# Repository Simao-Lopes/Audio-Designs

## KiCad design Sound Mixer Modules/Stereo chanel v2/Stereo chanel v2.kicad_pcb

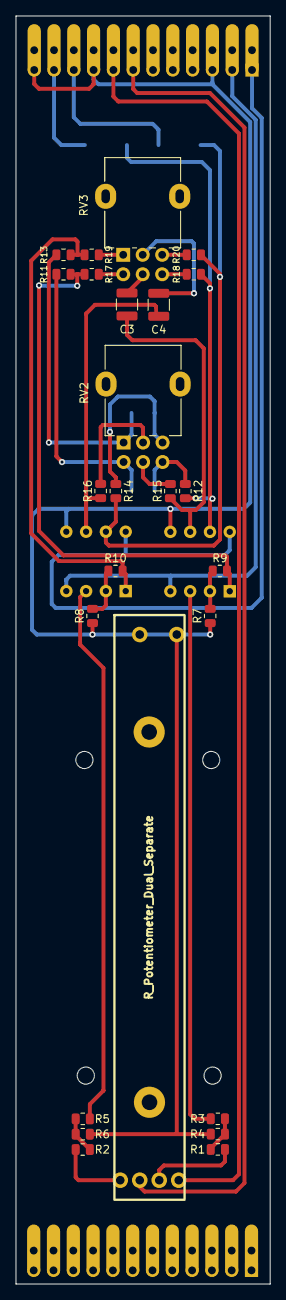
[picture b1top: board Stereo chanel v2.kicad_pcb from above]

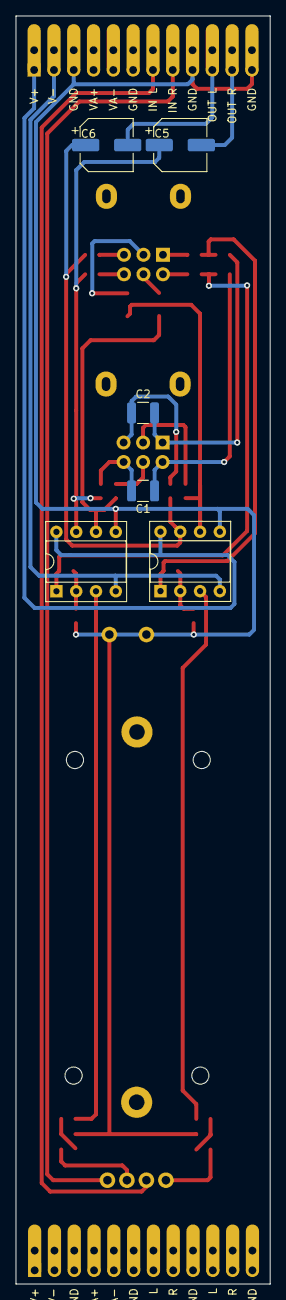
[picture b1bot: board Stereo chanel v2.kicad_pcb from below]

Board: 2 copper layers, 32.6 x 162.7 mm, 33 parts (8 on the bottom side), 33 nets.

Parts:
C1, C2: 47N; C_1210_3225Metric
C3, C4: 1N; C_1210_3225Metric
C5, C6: 10uf; CP_Elec_6.3x5.4_Nichicon
J1: Conector IO; PinHeader_2x12_P2.54mm_Vertical
J2: DUMMY; PinHeader_2x12_P2.54mm_Vertical
R1, R2, R3, R5: 2K2; R_0805_2012Metric
R4, R6: 100K; R_0805_2012Metric
R7, R8, R9, R10, R17, R18, R19, R20: 10K; R_0805_2012Metric
R11, R12, R13, R14, R15, R16: 22K; R_0805_2012Metric
RV1: R_Potentiometer_Dual_Separate; ALPS RS60112
RV2, RV3: R_Potentiometer_Dual_Separate; Potentiometer_Alpha_RD902F-40-00D_Dual_Vertical
U1, U2: NE5532; DIP-8_W7.62mm_Socket

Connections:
GND: J1.3, J1.9, J1.12, R4.1, R6.1, R7.1, R8.1, RV1.3, RV1.6, U1.5 (+), U2.5 (+)
L_INPUT: J1.7, RV1.1
L_OUTPUT: C6.2, J1.10
unnamed: C1.1, R11.1, RV2.4
unnamed: C1.2, R12.2, RV2.6
unnamed: C2.1, R13.1, RV2.1
unnamed: C2.2, R14.2, RV2.3
unnamed: C3.1, R15.1, U1.6 (-)
unnamed: C3.2, RV3.5
unnamed: C4.1, R16.1, U2.6 (-)
unnamed: C4.2, RV3.2
unnamed: C5.1, R12.1, R18.1, U1.7
unnamed: C6.1, R14.1, R20.1, U2.7
unnamed: R1.1, RV1.5
unnamed: R1.2, R3.1, R4.2
unnamed: R2.1, RV1.2
unnamed: R2.2, R5.1, R6.2
unnamed: R3.2, U1.3 (+)
unnamed: R5.2, U2.3 (+)
unnamed: R7.2, R9.2, U1.2 (-)
unnamed: R10.1, R13.2, R19.2, U2.1
unnamed: R8.2, R10.2, U2.2 (-)
unnamed: R9.1, R11.2, R17.2, U1.1
unnamed: R15.2, RV2.5
unnamed: R16.2, RV2.2
unnamed: R17.1, RV3.4
unnamed: R18.2, RV3.6
unnamed: R19.1, RV3.1
unnamed: R20.2, RV3.3
R_INPUT: J1.8, RV1.4
R_OUTPUT: C5.2, J1.11
VCC: J1.1, U1.8 (V+), U2.8 (V+)
VEE: J1.2, U1.4 (V-), U2.4 (V-)

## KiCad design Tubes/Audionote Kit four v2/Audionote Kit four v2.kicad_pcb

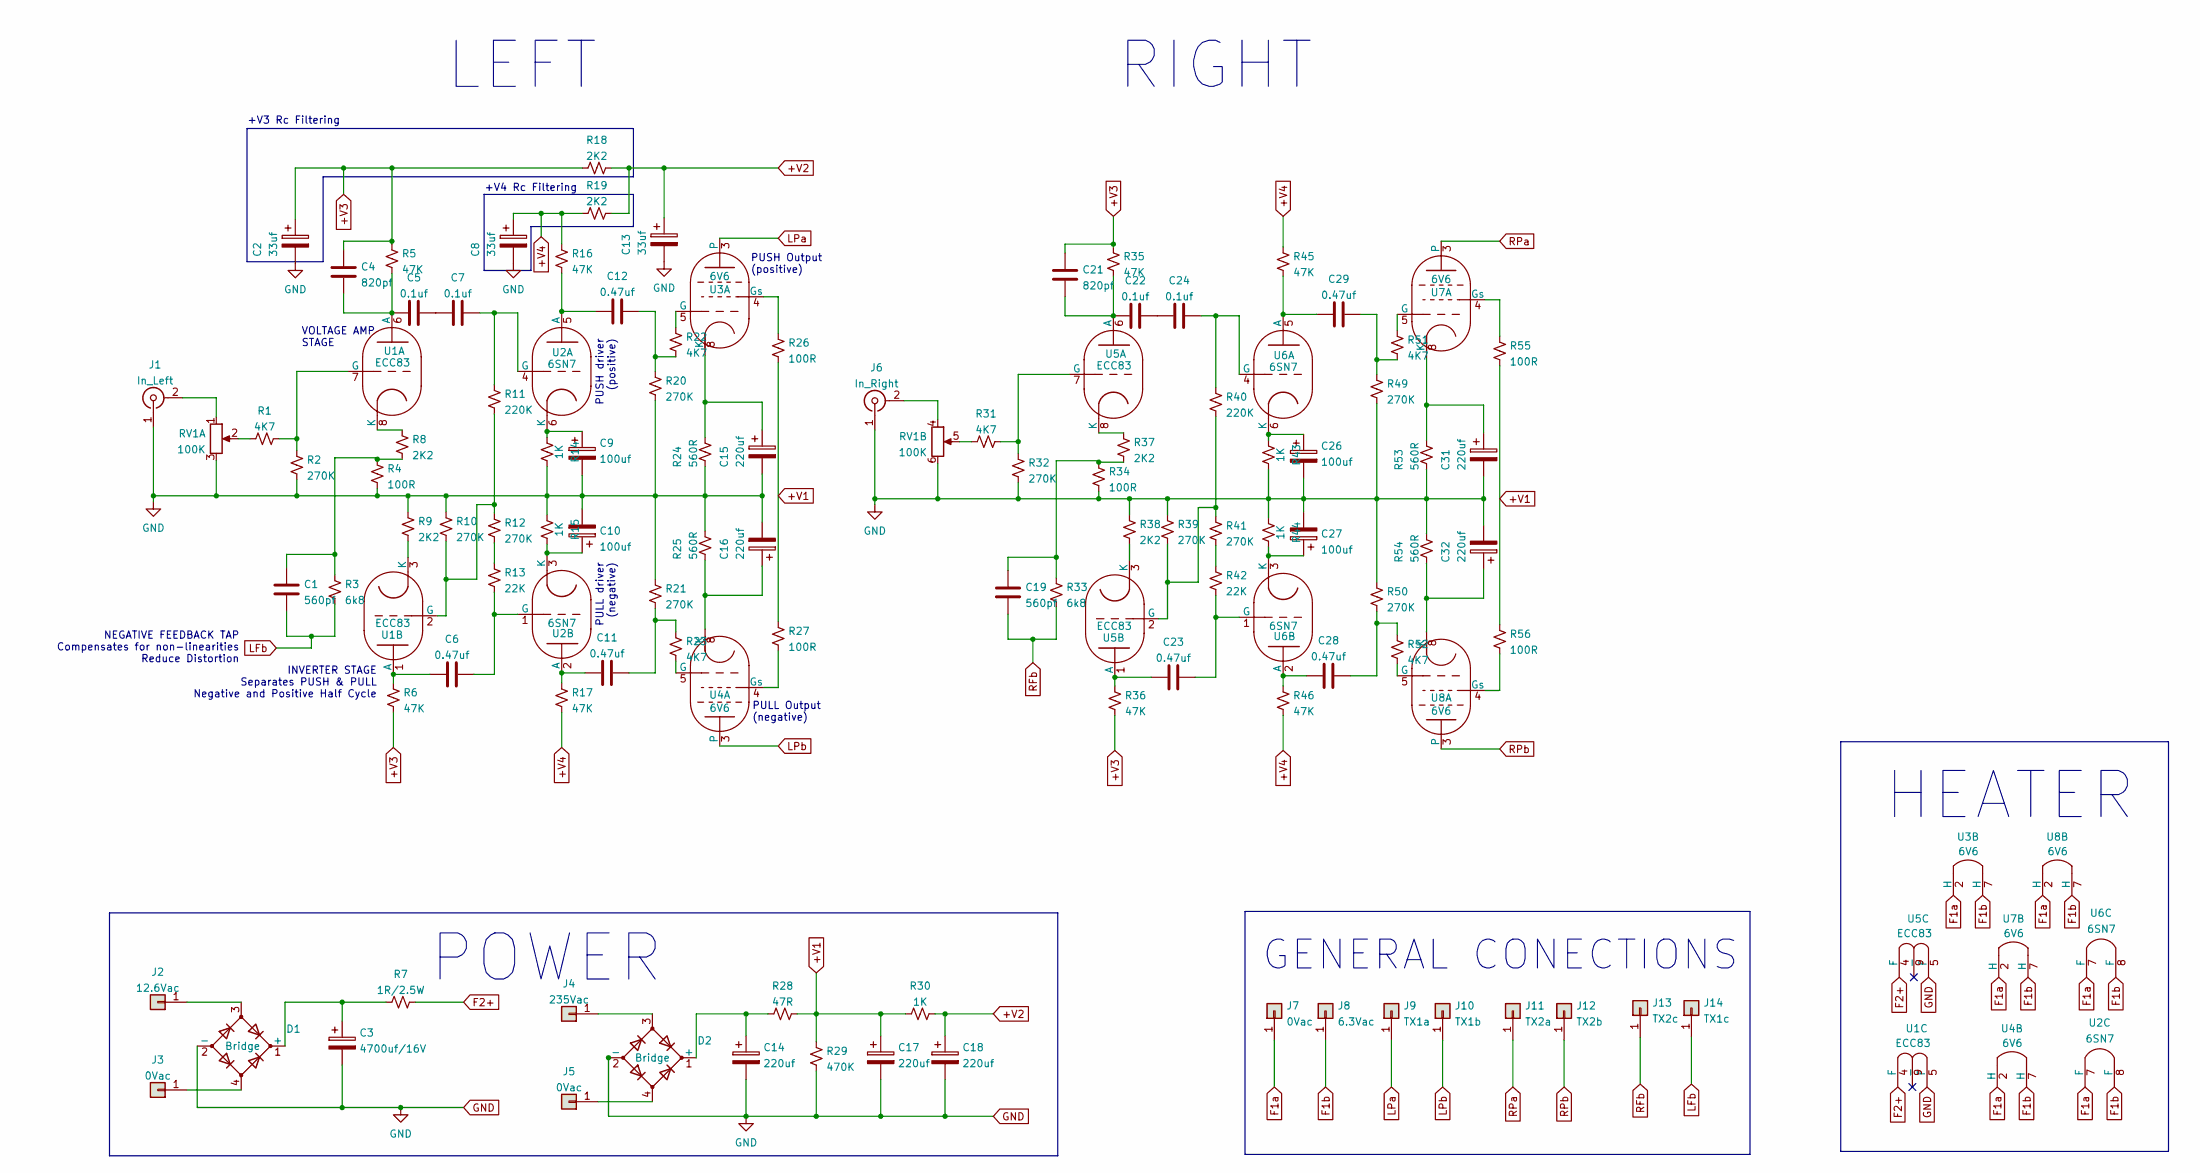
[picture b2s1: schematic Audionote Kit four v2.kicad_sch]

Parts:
C1, C19: 560pf; C_Rect_L7.2mm_W3.5mm_P5.00mm_FKS2_FKP2_MKS2_MKP2
C2, C8, C13: 33uf; CP_Radial_D10.0mm_P5.00mm_P7.50mm
C3: 4700uf/16V; C_Radial_D16.0mm_H31.5mm_P7.50mm
C4, C21: 820pf; C_Rect_L7.2mm_W3.5mm_P5.00mm_FKS2_FKP2_MKS2_MKP2
C5, C7, C22, C24: 0.1uf; C_Rect_L26.5mm_W6.0mm_P22.50mm_MKS4
C6, C11, C12, C23, C28, C29: 0.47uf; C_Rect_L31.5mm_W9.0mm_P27.50mm_MKS4
C9, C10, C26, C27: 100uf; CP_Radial_D6.3mm_P2.50mm
C14, C17, C18: 220uf; CP_Radial_D25.0mm_P10.00mm_SnapIn
C15, C16, C31, C32: 220uf; CP_Radial_D10.0mm_P5.00mm_P7.50mm
D1, D2: Bridge; Diode_Bridge_19.0x3.5x10.0mm_P5.0mm
J1: In_Left; SolderWire-0.75sqmm_1x02_P7mm_D1.25mm_OD3.5mm
J2: 12.6Vac; SolderWire-0.75sqmm_1x01_D1.25mm_OD2.3mm
J3, J5, J7: 0Vac; SolderWire-0.75sqmm_1x01_D1.25mm_OD2.3mm
J4: 235Vac; SolderWire-0.75sqmm_1x01_D1.25mm_OD2.3mm
J6: In_Right; SolderWire-0.75sqmm_1x02_P7mm_D1.25mm_OD3.5mm
J8: 6.3Vac; SolderWire-0.75sqmm_1x01_D1.25mm_OD2.3mm
J9: TX1a; SolderWire-0.75sqmm_1x01_D1.25mm_OD2.3mm
J10: TX1b; SolderWire-0.75sqmm_1x01_D1.25mm_OD2.3mm
J11: TX2a; SolderWire-0.75sqmm_1x01_D1.25mm_OD2.3mm
J12: TX2b; SolderWire-0.75sqmm_1x01_D1.25mm_OD2.3mm
J13: TX2c; SolderWire-0.75sqmm_1x01_D1.25mm_OD2.3mm
J14: TX1c; SolderWire-0.75sqmm_1x01_D1.25mm_OD2.3mm
R1, R22, R23, R31, R51, R52: 4K7; R_Axial_DIN0309_L9.0mm_D3.2mm_P12.70mm_Horizontal
R2, R10, R12, R20, R21, R32, R39, R41, R49, R50: 270K; R_Axial_DIN0309_L9.0mm_D3.2mm_P12.70mm_Horizontal
R3, R33: 6k8; R_Axial_DIN0309_L9.0mm_D3.2mm_P12.70mm_Horizontal
R4, R34: 100R; R_Axial_DIN0309_L9.0mm_D3.2mm_P12.70mm_Horizontal
R5, R6, R16, R17, R35, R36, R45, R46: 47K; R_Axial_DIN0309_L9.0mm_D3.2mm_P12.70mm_Horizontal
R7: 1R/2.5W; R_Axial_DIN0414_L11.9mm_D4.5mm_P15.24mm_Horizontal
R8, R9, R18, R19, R37, R38: 2K2; R_Axial_DIN0414_L11.9mm_D4.5mm_P15.24mm_Horizontal
R11, R40: 220K; R_Axial_DIN0309_L9.0mm_D3.2mm_P12.70mm_Horizontal
R13, R42: 22K; R_Axial_DIN0309_L9.0mm_D3.2mm_P12.70mm_Horizontal
R14, R15, R43, R44: 1K; R_Axial_DIN0309_L9.0mm_D3.2mm_P12.70mm_Horizontal
R24, R25, R53, R54: 560R; R_Axial_DIN0414_L11.9mm_D4.5mm_P15.24mm_Horizontal
R26, R27, R55, R56: 100R; R_Axial_DIN0414_L11.9mm_D4.5mm_P15.24mm_Horizontal
R28: 47R; R_Axial_Power_L25.0mm_W9.0mm_P27.94mm
R29: 470K; R_Axial_Power_L25.0mm_W9.0mm_P27.94mm
R30: 1K; R_Axial_Power_L25.0mm_W9.0mm_P27.94mm
RV1: 100K; Potentiometer_Alps_RK097_Dual_Horizontal
U1, U5: ECC83; Valve_Noval_P
U2, U6: 6SN7; Valve_Octal
U3, U4, U7, U8: 6V6; Valve_Octal

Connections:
+V1: C17.1, R26.2, R27.1, R28.2, R29.2, R30.1, R55.2, R56.1
+V2: C13.1, C18.1, R18.1, R19.1, R30.2
+V3: C2.1, C4.1, C21.1, R5.2, R6.1, R18.2, R35.2, R36.1; also elsewhere on the board
+V4: C8.1, R16.2, R17.1, R19.2, R45.2, R46.1
F1a: J7.1, U2.7 (F), U3.2 (H), U4.2 (H), U6.7 (F), U7.2 (H), U8.2 (H); also elsewhere on the board
F1b: J8.1, U2.8 (F), U3.7 (H), U4.7 (H), U6.8 (F), U7.7 (H), U8.7 (H); also elsewhere on the board
F2+: R7.2, U1.4 (F), U5.4 (F)
GND: C2.2, C3.2, C8.2, C9.2, C10.2, C13.2, C14.2, C15.2, C16.2, C17.2, C18.2, C26.2, C27.2, C31.2, C32.2, D1.2 (-), D2.2 (-), J1.1 (In), J6.1 (In), R2.1, R4.1, R9.2, R10.2, R14.2, R15.1, R20.1, R21.2, R24.1, R25.1, R29.1, R32.1, R34.1, R38.2, R39.2, R43.2, R44.1, R49.1, R50.2, R53.1, R54.1, RV1.3, RV1.6, U1.5 (F), U5.5 (F); also elsewhere on the board
LFb: C1.1, J14.1, R3.2; also elsewhere on the board
LPa: J9.1, U3.3
LPb: J10.1, U4.3
unnamed 11: C1.2, R3.1, R4.2, R8.1; also elsewhere on the board
unnamed: C3.1, D1.1 (+), R7.1
unnamed 13: C4.2, C5.1, R5.1, U1.6 (A); also elsewhere on the board
unnamed: C5.2, C7.1
unnamed: C6.1, R6.2, U1.1 (A)
unnamed: C6.2, R13.1, U2.1 (G)
unnamed: C7.2, R11.2, U2.4 (G)
unnamed: C9.1, R14.1, U2.6 (K)
unnamed: C10.1, R15.2, U2.3 (K)
unnamed: C11.1, R17.2, U2.2 (A)
unnamed: C11.2, R21.1, R23.2
unnamed: C12.1, R16.1, U2.5 (A)
unnamed: C12.2, R20.2, R22.1
unnamed: C14.1, D2.1 (+), R28.1
unnamed: C15.1, R24.2, U3.8 (K)
unnamed: C16.1, R25.2, U4.8 (K)
unnamed: C19.2, R33.1, R34.2, R37.1
unnamed 28: C21.2, C22.1, R35.1, U5.6 (A); also elsewhere on the board
unnamed: C22.2, C24.1
unnamed: C23.1, R36.2, U5.1 (A)
unnamed: C23.2, R42.1, U6.1 (G)
unnamed: C24.2, R40.2, U6.4 (G)
unnamed: C26.1, R43.1, U6.6 (K)
unnamed: C27.1, R44.2, U6.3 (K)
unnamed: C28.1, R46.2, U6.2 (A)
unnamed: C28.2, R50.1, R52.2
unnamed: C29.1, R45.1, U6.5 (A)
unnamed: C29.2, R49.2, R51.1
unnamed: C31.1, R53.2, U7.8 (K)
unnamed: C32.1, R54.2, U8.8 (K)
unnamed: D1.3, J2.1
unnamed: D1.4, J3.1
unnamed: D2.3, J4.1
unnamed: D2.4, J5.1
unnamed: J1.2 (Ext), RV1.1
unnamed: J6.2 (Ext), RV1.4
unnamed 47: R1.1, RV1.2; also elsewhere on the board
unnamed: R1.2, R2.2, U1.7 (G)
unnamed: R8.2, U1.8 (K)
unnamed: R9.1, U1.3 (K)
unnamed: R10.1, R11.1, R12.2, U1.2 (G)
unnamed: R12.1, R13.2
unnamed: R22.2, U3.5 (G)
unnamed: R23.1, U4.5 (G)
unnamed: R26.1, U3.4 (Gs)
unnamed: R27.2, U4.4 (Gs)
unnamed 57: R31.1, RV1.5; also elsewhere on the board
unnamed: R31.2, R32.2, U5.7 (G)
unnamed: R37.2, U5.8 (K)
unnamed: R38.1, U5.3 (K)
unnamed: R39.1, R40.1, R41.2, U5.2 (G)
unnamed: R41.1, R42.2
unnamed: R51.2, U7.5 (G)
unnamed: R52.1, U8.5 (G)
unnamed: R55.1, U7.4 (Gs)
unnamed: R56.2, U8.4 (Gs)
RFb: C19.1, J13.1, R33.2; also elsewhere on the board
RPa: J11.1, U7.3
RPb: J12.1, U8.3

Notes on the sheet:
GENERAL CONECTIONS
+V4 Rc Filtering
INVERTER STAGE Separates PUSH & PULL Negative and Positive Half Cycle
RIGHT
VOLTAGE AMP STAGE
POWER
PUSH driver (positive)
PUSH Output (positive)
NEGATIVE FEEDBACK TAP Compensates for non-linearities Reduce Distortion
PULL driver (negative)
PULL Output (negative)
LEFT
+V3 Rc Filtering
HEATER

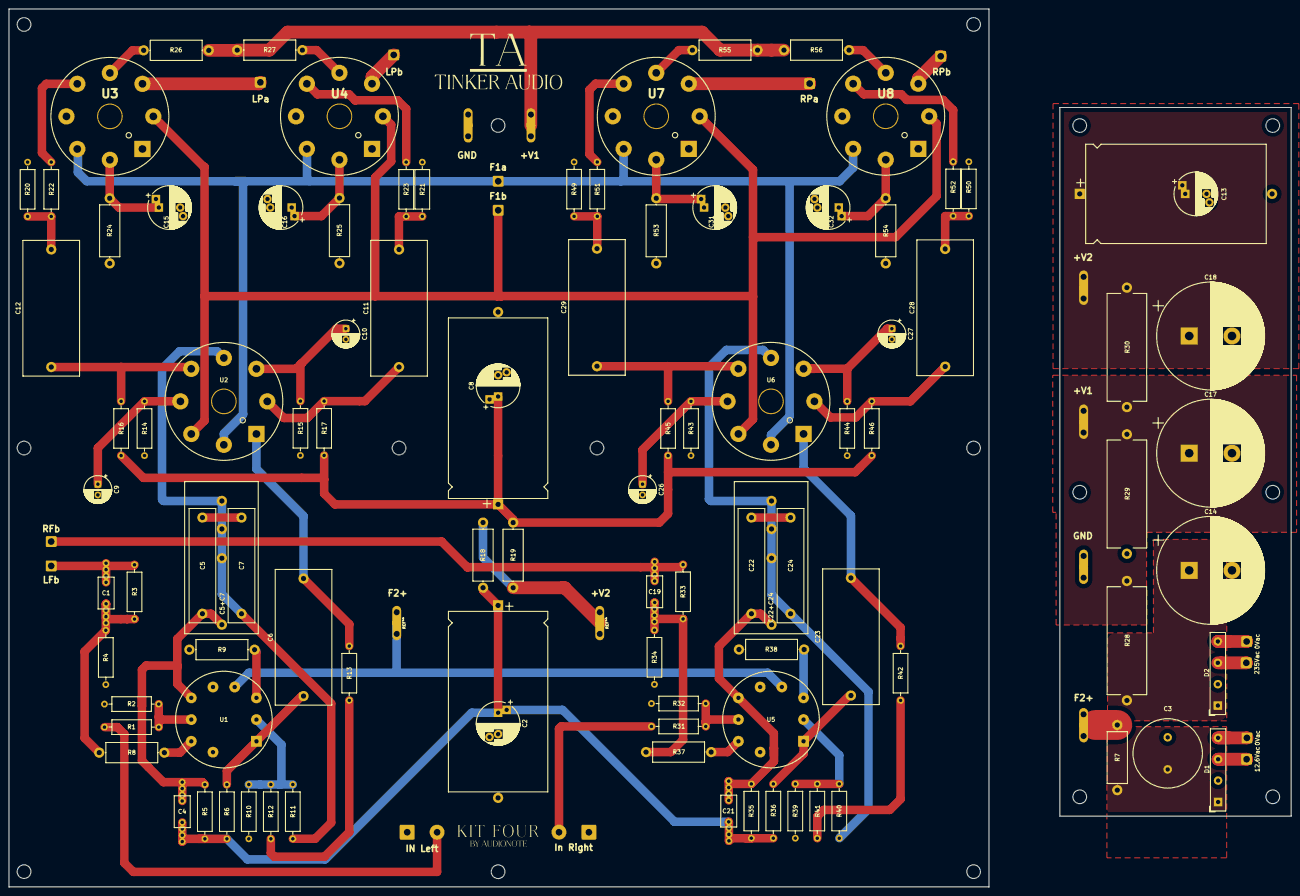
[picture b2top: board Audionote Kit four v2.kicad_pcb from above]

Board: 2 copper layers, 229.2 x 205.4 mm, 117 parts (0 on the bottom side), 68 nets.

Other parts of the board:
1, 2, 3, 4, 5, 6, 7, 8, 9, 10: (no value)
F1a: 6.3Vac; SolderWire-0.75sqmm_1x01_D1.25mm_OD2.3mm
F1b: 0Vac; SolderWire-0.75sqmm_1x01_D1.25mm_OD2.3mm
IN Left: In_Left; SolderWire-0.75sqmm_1x02_P7mm_D1.25mm_OD3.5mm
In Right : In_Right; SolderWire-0.75sqmm_1x02_P7mm_D1.25mm_OD3.5mm
LFb: TX1c; SolderWire-0.75sqmm_1x01_D1.25mm_OD2.3mm
RFb: TX2c; SolderWire-0.75sqmm_1x01_D1.25mm_OD2.3mm

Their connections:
+V3: 3.1, 4.1, 5.1, 6.1; also elsewhere on the board
F1a: F1b.1; also elsewhere on the board
F1b: F1a.1; also elsewhere on the board
GND: IN Left.1 (In), In Right.1 (In); also elsewhere on the board
LFb: LFb.1; also elsewhere on the board
unnamed 11: 9.2, 10.2; also elsewhere on the board
unnamed 13: 7.2, 8.2; also elsewhere on the board
unnamed 28: 1.2, 2.2; also elsewhere on the board
unnamed 47: IN Left.2 (Ext); also elsewhere on the board
unnamed 57: In Right.2 (Ext); also elsewhere on the board
RFb: RFb.1; also elsewhere on the board

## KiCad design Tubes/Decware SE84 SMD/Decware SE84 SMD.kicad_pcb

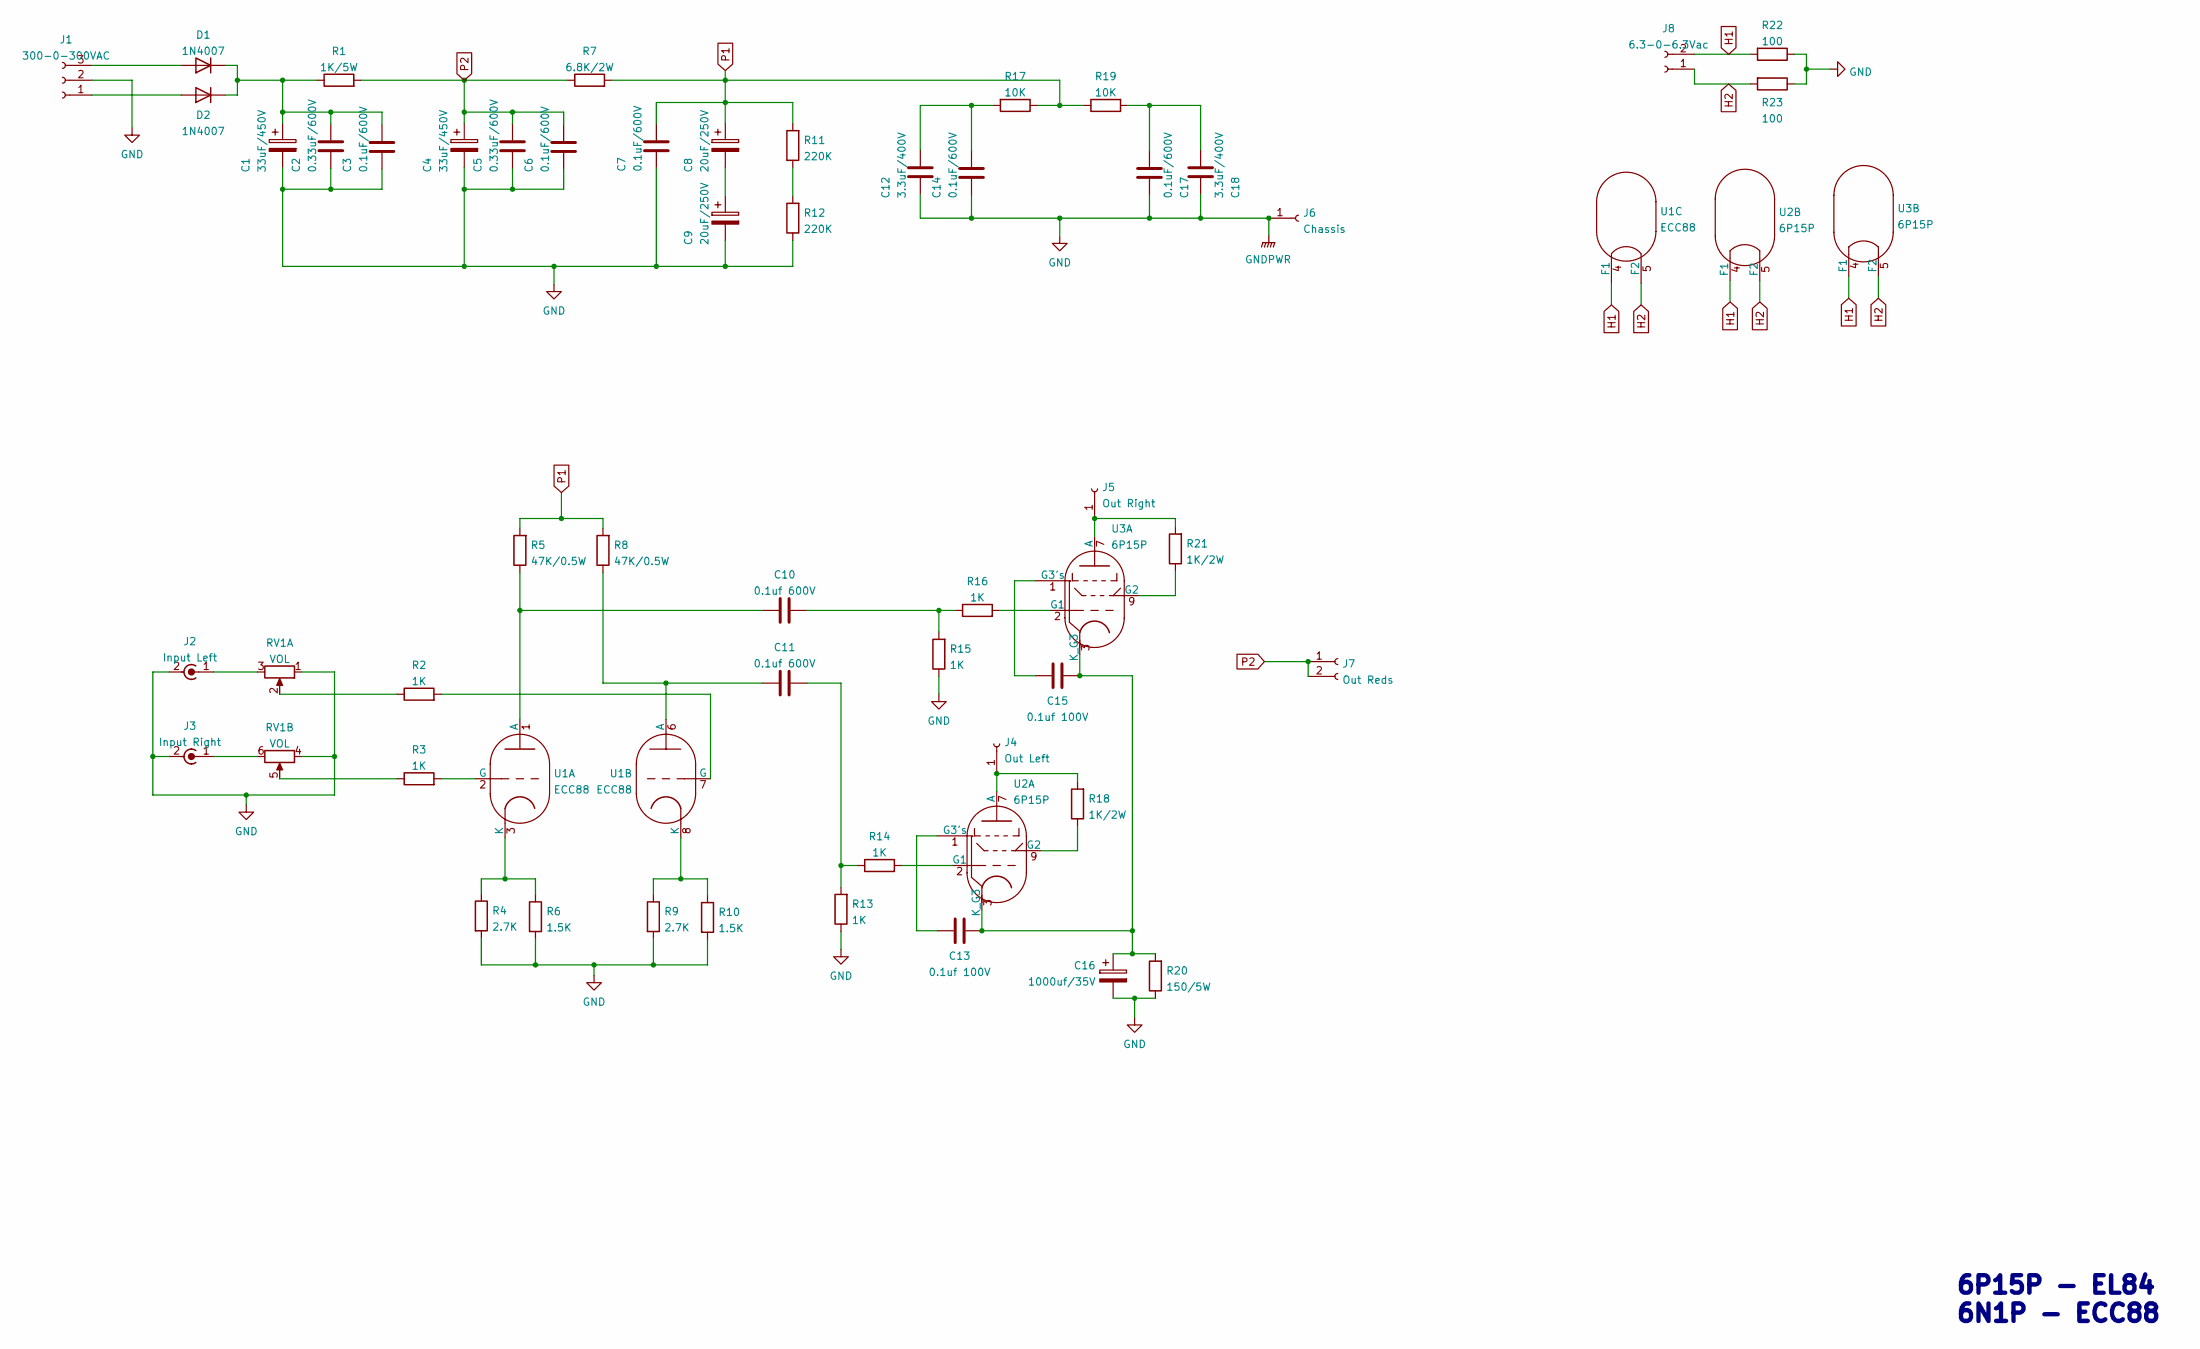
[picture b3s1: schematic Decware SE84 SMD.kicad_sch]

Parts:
C1, C4: 33uF/450V; CP_Radial_D18.0mm_P7.50mm
C2, C5: 0.33uF/600V; CP_Axial_L29.0mm_D20.0mm_P35.00mm_Horizontal
C3, C6, C7, C14, C17: 0.1uF/600V; C_Rect_L7.2mm_W7.2mm_P5.00mm_FKS2_FKP2_MKS2_MKP2
C8, C9: 20uF/250V; CP_Axial_L40.0mm_D16.0mm_P48.00mm_Horizontal
C10, C11: 0.1uf 600V; C_Rect_L7.2mm_W7.2mm_P5.00mm_FKS2_FKP2_MKS2_MKP2
C12, C18: 3.3uF/400V; C_Rect_L41.5mm_W20.0mm_P37.50mm_MKS4
C13, C15: 0.1uf 100V; C_Rect_L7.2mm_W7.2mm_P5.00mm_FKS2_FKP2_MKS2_MKP2
C16: 1000uf/35V; CP_Radial_D22.0mm_P10.00mm_SnapIn
D1, D2: 1N4007; D_DO-41_SOD81_P10.16mm_Horizontal
J1: 300-0-300VAC; SolderWire-0.5sqmm_1x03_P4.8mm_D0.9mm_OD2.3mm
J2: Input Left; RCA PANEL 2PIN FOOTPRINT
J3: Input Right; RCA PANEL 2PIN FOOTPRINT
J4: Out Left; SolderWire-0.5sqmm_1x01_D0.9mm_OD2.3mm
J5: Out Right; SolderWire-0.5sqmm_1x01_D0.9mm_OD2.3mm
J6: Chassis; MountingHole_3.2mm_M3_DIN965_Pad
J7: Out Reds; SolderWire-0.5sqmm_1x02_P4.8mm_D0.9mm_OD2.3mm
J8: 6.3-0-6.3Vac; SolderWire-0.5sqmm_1x02_P4.8mm_D0.9mm_OD2.3mm
R1: 1K/5W; R_Axial_DIN0922_L20.0mm_D9.0mm_P30.48mm_Horizontal
R2, R3, R13, R14, R15, R16: 1K; R_1206_3216Metric_Pad1.30x1.75mm_HandSolder
R4, R9: 2.7K; R_1206_3216Metric_Pad1.30x1.75mm_HandSolder
R5, R8: 47K/0.5W; R_1206_3216Metric_Pad1.30x1.75mm_HandSolder
R6, R10: 1.5K; R_1206_3216Metric_Pad1.30x1.75mm_HandSolder
R7: 6.8K/2W; R_2512_6332Metric
R11, R12: 220K; R_1206_3216Metric_Pad1.30x1.75mm_HandSolder
R17, R19: 10K; R_1206_3216Metric_Pad1.30x1.75mm_HandSolder
R18, R21: 1K/2W; R_2512_6332Metric
R20: 150/5W; R_Axial_DIN0922_L20.0mm_D9.0mm_P30.48mm_Horizontal
R22, R23: 100; R_1206_3216Metric_Pad1.30x1.75mm_HandSolder
RV1: VOL; Potentiometer_Alps_RK271_Dual_Horizontal
U1: ECC88; Valve_Noval_P
U2, U3: 6P15P; Valve_Noval_P

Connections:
GND: C1.2, C2.2, C3.2, C4.2, C5.2, C6.2, C7.2, C9.2, C12.2, C14.2, C16.2, C17.2, C18.2, J1.2, J2.2 (Ext), J3.2 (Ext), J6.1, R4.2, R6.2, R9.2, R10.2, R12.1, R13.1, R15.1, R20.1, R22.1, R23.1, RV1.1, RV1.4; also elsewhere on the board
H1: J8.2, R22.2, U1.4 (F1), U2.4 (F1), U3.4 (F1)
H2: J8.1, R23.2, U1.5 (F2), U2.5 (F2), U3.5 (F2)
unnamed: C1.1, C2.1, C3.1, D1.1 (K), D2.1 (K), R1.1
unnamed: C8.2, C9.1
unnamed: C10.1, R5.1, U1.1 (A)
unnamed: C10.2, R15.2, R16.1
unnamed: C11.1, R8.1, U1.6 (A)
unnamed: C11.2, R13.2, R14.1
unnamed: C12.1, C14.1, R17.2
unnamed: C13.1, U2.1 (G3's)
unnamed: C13.2, C15.2, C16.1, R20.2, U2.3 (K_G3), U3.3 (K_G3)
unnamed: C15.1, U3.1 (G3's)
unnamed: C17.1, C18.1, R19.2
unnamed: D1.2 (A), J1.3
unnamed: D2.2 (A), J1.1
unnamed: J2.1 (In), RV1.3
unnamed: J3.1 (In), RV1.6
unnamed: J4.1, R18.2, U2.7 (A)
unnamed: J5.1, R21.2, U3.7 (A)
unnamed: R2.1, RV1.2
unnamed: R2.2, U1.7 (G)
unnamed: R3.1, RV1.5
unnamed: R3.2, U1.2 (G)
unnamed: R4.1, R6.1, U1.3 (K)
unnamed: R9.1, R10.1, U1.8 (K)
unnamed: R11.1, R12.2
unnamed: R14.2, U2.2 (G1)
unnamed: R16.2, U3.2 (G1)
unnamed: R18.1, U2.9 (G2)
unnamed: R21.1, U3.9 (G2)
P1: C7.1, C8.1, R5.2, R7.2, R8.2, R11.2, R17.1, R19.1
P2: C4.1, C5.1, C6.1, J7.1, J7.2, R1.2, R7.1

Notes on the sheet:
6P15P - EL84 6N1P - ECC88

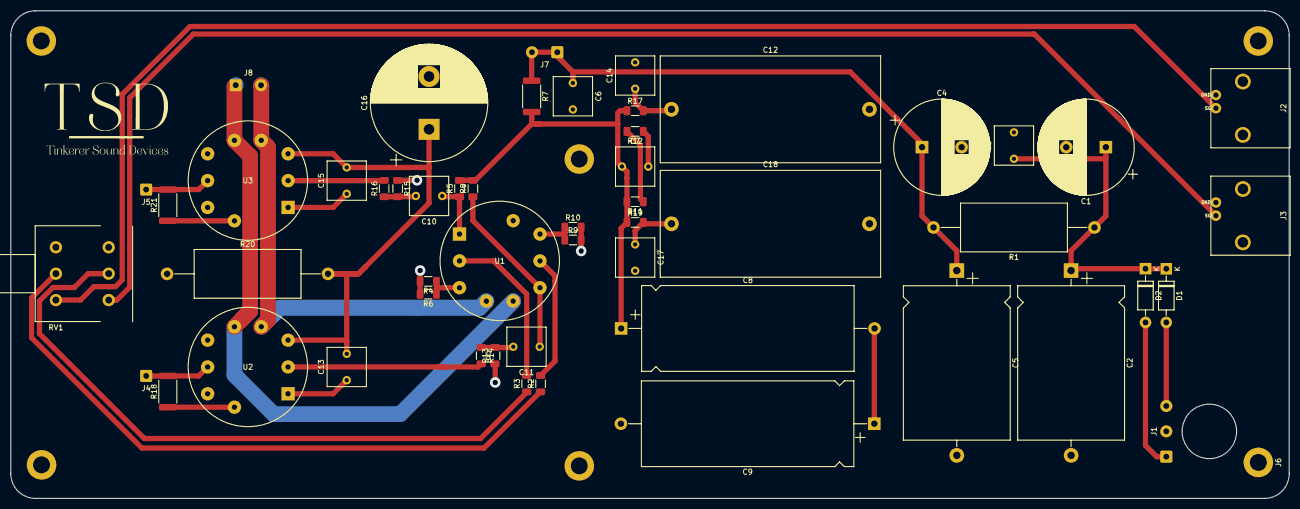
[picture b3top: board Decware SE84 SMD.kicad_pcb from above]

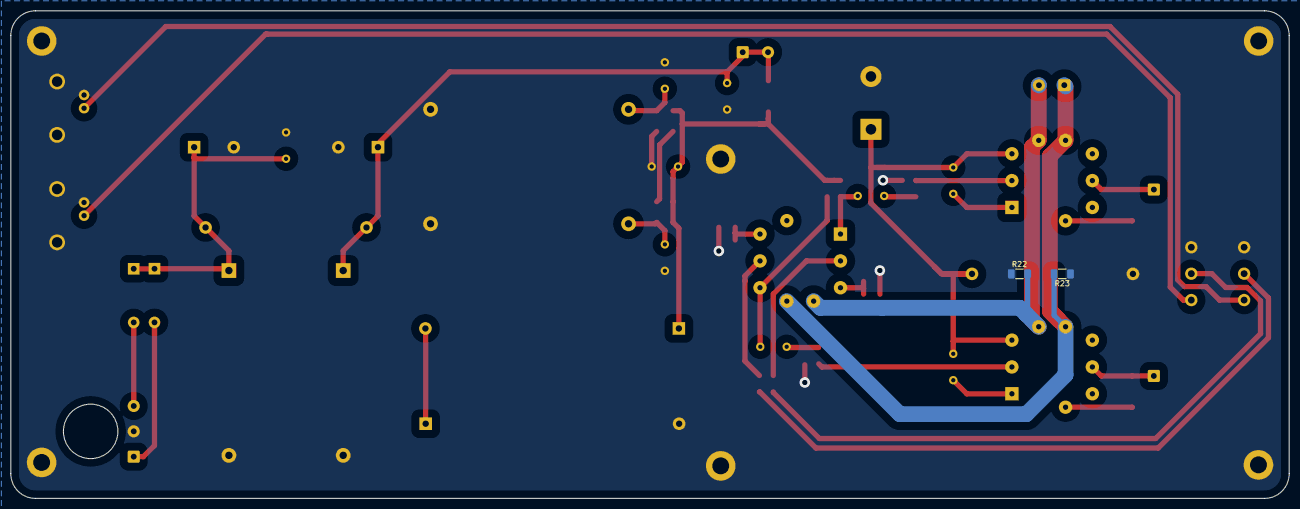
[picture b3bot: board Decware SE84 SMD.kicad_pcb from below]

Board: 2 copper layers, 242.1 x 92.3 mm, 60 parts (2 on the bottom side), 33 nets.

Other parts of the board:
J6#2, J6#3, J6#4, J6#5, J6#6: Chassis; MountingHole_3.2mm_M3_DIN965_Pad

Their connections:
GND: J6#2.1, J6#3.1, J6#4.1, J6#5.1, J6#6.1; also elsewhere on the board

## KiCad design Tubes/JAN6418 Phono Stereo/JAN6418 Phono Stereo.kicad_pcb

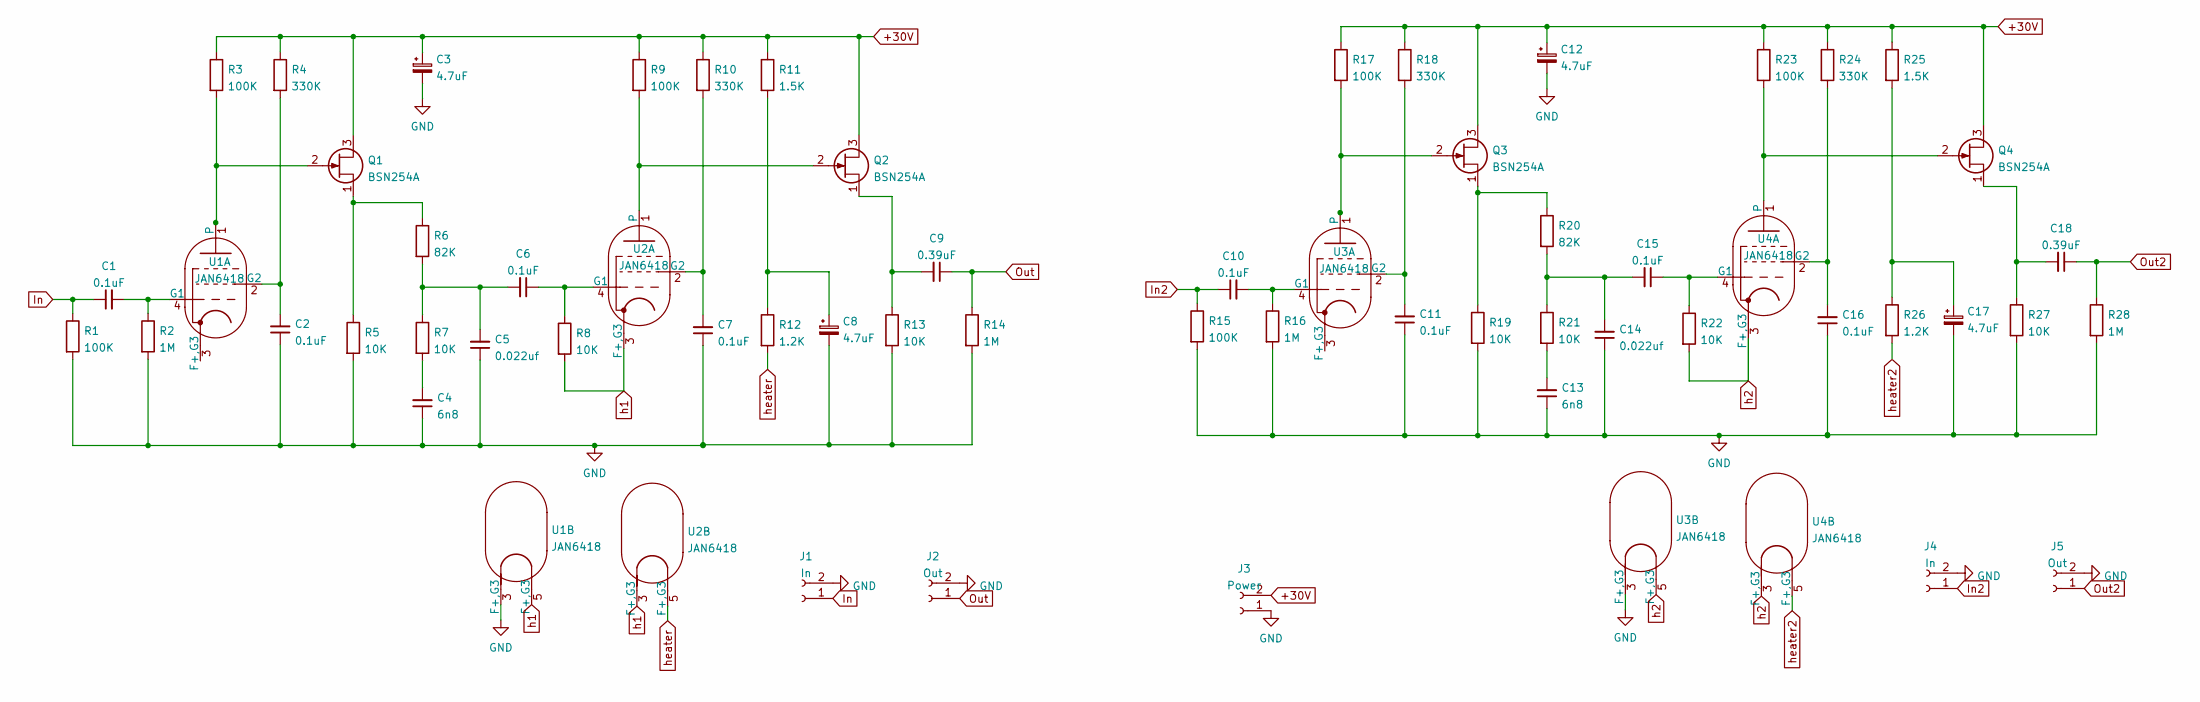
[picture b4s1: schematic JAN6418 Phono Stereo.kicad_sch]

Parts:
C1, C2, C6, C7, C10, C11, C15, C16: 0.1uF; C_Rect_L10.0mm_W2.5mm_P7.50mm_MKS4
C3, C8, C12, C17: 4.7uF; CP_Radial_D5.0mm_P2.50mm
C4, C13: 6n8; C_Rect_L10.0mm_W2.5mm_P7.50mm_MKS4
C5, C14: 0.022uf; C_Rect_L10.0mm_W2.5mm_P7.50mm_MKS4
C9, C18: 0.39uF; C_Rect_L10.0mm_W2.5mm_P7.50mm_MKS4
J1, J4: In; RCA PANEL 2PIN FOOTPRINT
J2, J5: Out; RCA PANEL 2PIN FOOTPRINT
J3: Power; TerminalBlock_TE_282834-2_1x02_P2.54mm_Horizontal
Q1, Q2, Q3, Q4: BSN254A; TO-92_Inline
R1, R3, R9, R15, R17, R23: 100K; R_Axial_DIN0207_L6.3mm_D2.5mm_P10.16mm_Horizontal
R2, R14, R16, R28: 1M; R_Axial_DIN0207_L6.3mm_D2.5mm_P10.16mm_Horizontal
R4, R10, R18, R24: 330K; R_Axial_DIN0207_L6.3mm_D2.5mm_P10.16mm_Horizontal
R5, R7, R8, R13, R19, R21, R22, R27: 10K; R_Axial_DIN0207_L6.3mm_D2.5mm_P10.16mm_Horizontal
R6, R20: 82K; R_Axial_DIN0207_L6.3mm_D2.5mm_P10.16mm_Horizontal
R11, R25: 1.5K; R_Axial_DIN0207_L6.3mm_D2.5mm_P10.16mm_Horizontal
R12, R26: 1.2K; R_Axial_DIN0207_L6.3mm_D2.5mm_P10.16mm_Horizontal
U1, U2, U3, U4: JAN6418; Valve_Mini_Pentode_Linear

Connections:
+30V: C3.1, C12.1, J3.2, Q1.3 (S), Q2.3 (S), Q3.3 (S), Q4.3 (S), R3.1, R4.1, R9.1, R10.1, R11.1, R17.1, R18.1, R23.1, R24.1, R25.1
GND: C2.1, C3.2, C4.1, C5.1, C7.1, C8.2, C11.1, C12.2, C13.1, C14.1, C16.1, C17.2, J1.2, J2.2, J3.1, J4.2, J5.2, R1.2, R2.2, R5.2, R13.2, R14.2, R15.2, R16.2, R19.2, R27.2, R28.2, U1.3 (F+,G3), U3.3 (F+,G3); also elsewhere on the board
In: C1.1, J1.1, R1.1; also elsewhere on the board
In2: C10.1, J4.1, R15.1; also elsewhere on the board
unnamed: C1.2, R2.1, U1.4 (G1)
unnamed: C2.2, R4.2, U1.2 (G2)
unnamed: C4.2, R7.2
unnamed: C5.2, C6.2, R6.2, R7.1
unnamed: C6.1, R8.1, U2.4 (G1)
unnamed: C7.2, R10.2, U2.2 (G2)
unnamed: C8.1, R11.2, R12.1
unnamed: C9.2, Q2.1 (D), R13.1
unnamed: C10.2, R16.1, U3.4 (G1)
unnamed: C11.2, R18.2, U3.2 (G2)
unnamed: C13.2, R21.2
unnamed: C14.2, C15.2, R20.2, R21.1
unnamed: C15.1, R22.1, U4.4 (G1)
unnamed: C16.2, R24.2, U4.2 (G2)
unnamed: C17.1, R25.2, R26.1
unnamed: C18.2, Q4.1 (D), R27.1
unnamed: Q1.1 (D), R5.1, R6.1
unnamed: Q1.2 (G), R3.2, U1.1
unnamed: Q2.2 (G), R9.2, U2.1
unnamed: Q3.1 (D), R19.1, R20.1
unnamed: Q3.2 (G), R17.2, U3.1
unnamed: Q4.2 (G), R23.2, U4.1
Out: C9.1, J2.1, R14.1; also elsewhere on the board
Out2: C18.1, J5.1, R28.1; also elsewhere on the board
h1: R8.2, U1.5 (F+,G3), U2.3 (F+,G3)
h2: R22.2, U3.5 (F+,G3), U4.3 (F+,G3)
heater: R12.2, U2.5 (F+,G3)
heater2: R26.2, U4.5 (F+,G3)

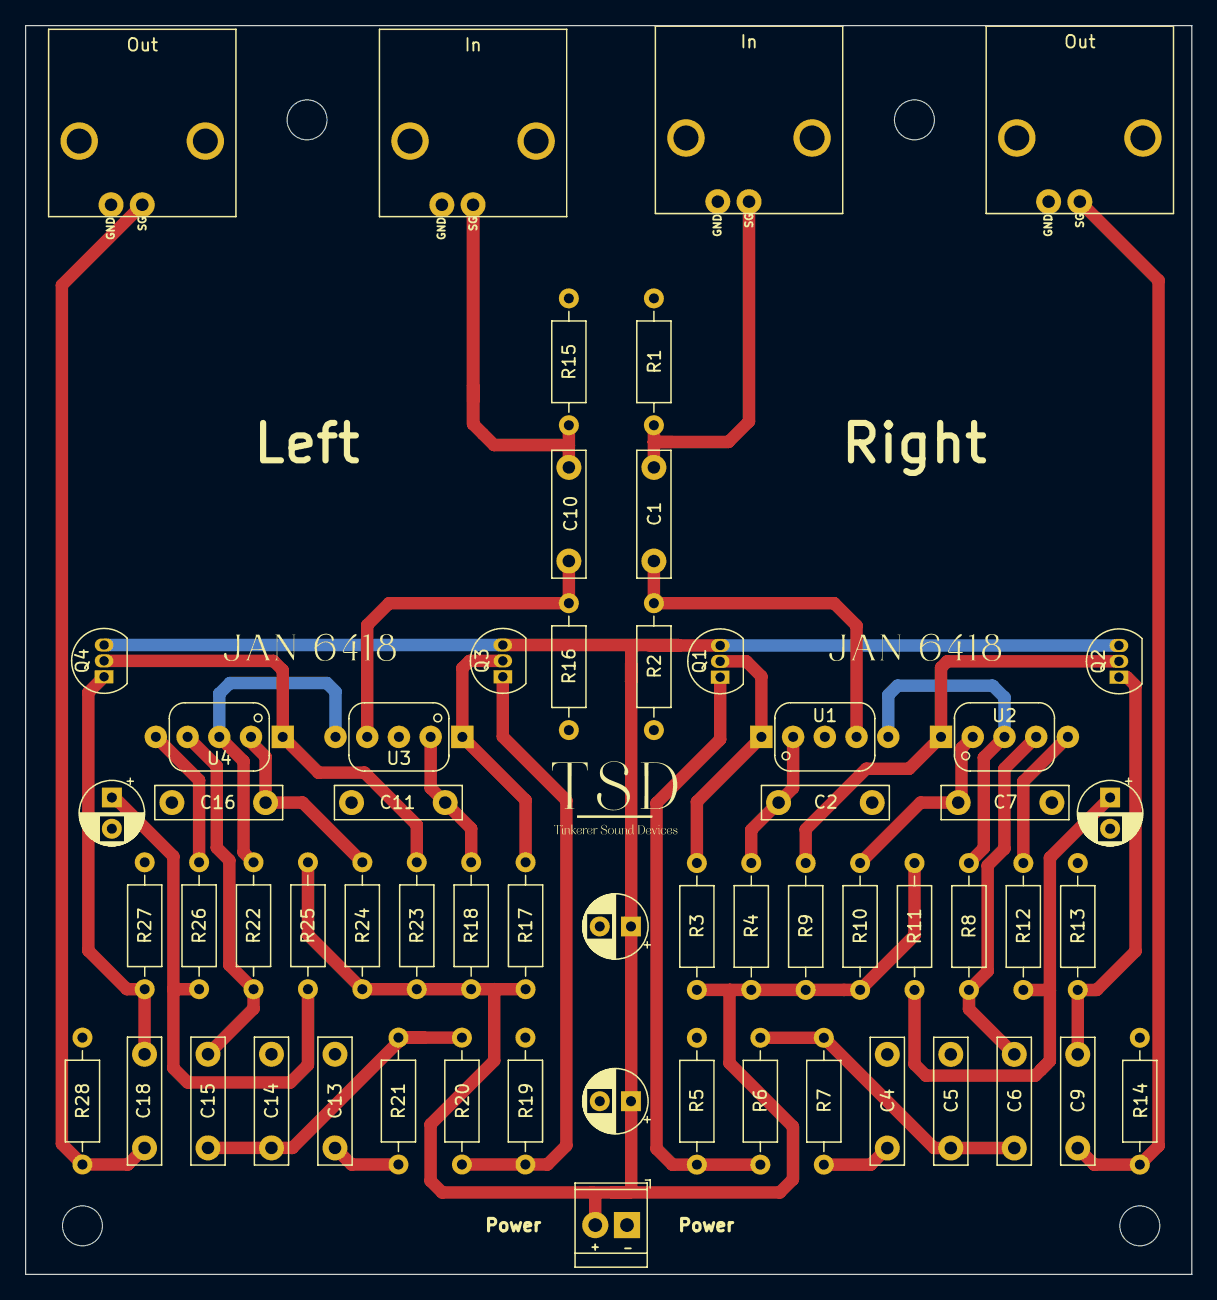
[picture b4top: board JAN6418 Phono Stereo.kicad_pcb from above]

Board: 2 copper layers, 93.4 x 100.0 mm, 59 parts (0 on the bottom side), 32 nets.

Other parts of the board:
In: In; RCA PANEL 2PIN FOOTPRINT
In#2: In; RCA PANEL 2PIN FOOTPRINT
Out: Out; RCA PANEL 2PIN FOOTPRINT
Out#2: Out; RCA PANEL 2PIN FOOTPRINT

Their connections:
GND: In.2, In#2.2, Out.2, Out#2.2; also elsewhere on the board
In: In.1; also elsewhere on the board
In2: In#2.1; also elsewhere on the board
Out: Out#2.1; also elsewhere on the board
Out2: Out.1; also elsewhere on the board

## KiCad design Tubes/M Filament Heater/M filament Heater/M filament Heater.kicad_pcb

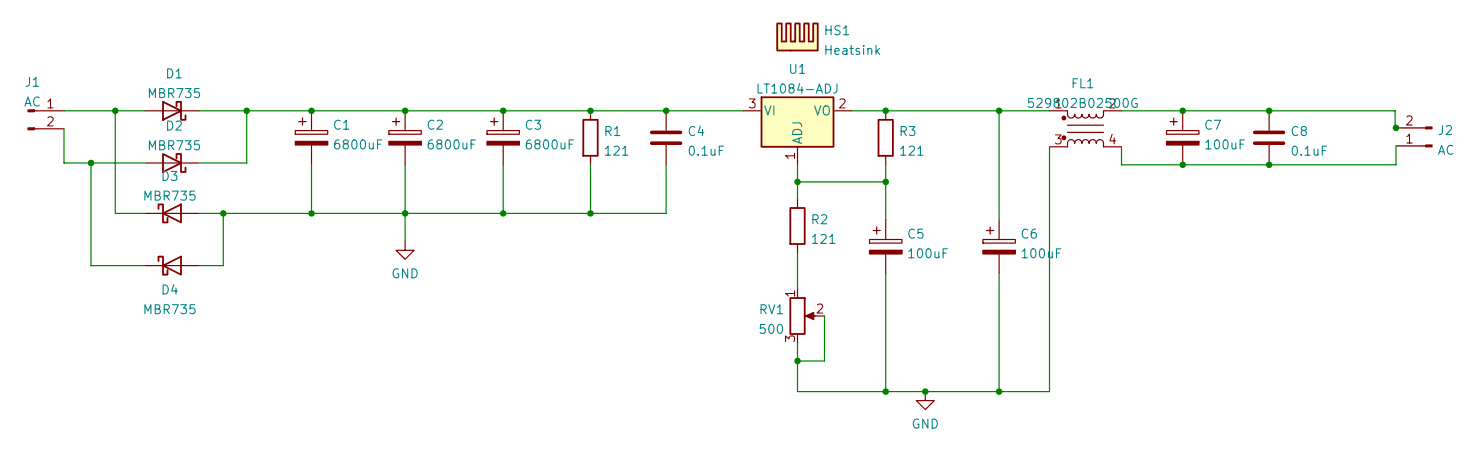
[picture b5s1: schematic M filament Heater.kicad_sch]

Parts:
C1, C2, C3: 6800uF; CP_Radial_D16.0mm_P7.50mm
C4, C8: 0.1uF; C_Rect_L7.2mm_W5.5mm_P5.00mm_FKS2_FKP2_MKS2_MKP2
C5, C6, C7: 100uF; CP_Radial_D10.0mm_P5.00mm_P7.50mm
D1, D2, D3, D4: MBR735; TO-220-2_Vertical
FL1: 529802B02500G; Choke_Schaffner_RN218-04-12.5x18.0mm
HS1: Heatsink; AAvid_Heatsink
J1, J2: AC; TerminalBlock_RND_205-00012_1x02_P5.00mm_Horizontal
R1, R2, R3: 121; R_Axial_DIN0309_L9.0mm_D3.2mm_P15.24mm_Horizontal
RV1: 500; Potentiometer_Bourns_3296W_Vertical
U1: LT1084-ADJ; TO-220-3_Vertical

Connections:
GND: C1.2, C2.2, C3.2, C4.2, C5.2, C6.2, D3.2 (A), D4.2 (A), FL1.3, R1.2, RV1.2, RV1.3
unnamed: C1.1, C2.1, C3.1, C4.1, D1.1 (K), D2.1 (K), R1.1, U1.3 (VI)
unnamed: C5.1, R2.1, R3.2, U1.1 (ADJ)
unnamed: C6.1, FL1.1, R3.1, U1.2 (VO)
unnamed: C7.1, C8.1, FL1.2, J2.2
unnamed: C7.2, C8.2, FL1.4, J2.1
unnamed: D1.2 (A), D3.1 (K), J1.1
unnamed: D2.2 (A), D4.1 (K), J1.2
unnamed: R2.2, RV1.1
